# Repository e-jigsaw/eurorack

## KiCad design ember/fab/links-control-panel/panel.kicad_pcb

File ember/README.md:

# ember

Mutable Instruments モジュール群を tscircuit (TypeScript / React ベースの回路 + PCB 設計) に順次再構築するアセット集。

## 方針

- 単発移植ではなく、Eurorack 共通プリミティブと回路ブロックをアセットとして積み上げる
- EAGLE 資産を高忠実度で持ち上げる方向は採らない (PDF 再構築や Eagle 変換ツールは `../archive/` 配下)
- 「KiCad で書いたほうが速い」と感じても、アセット化を優先

## 試作台

Mutable Instruments **Links** v4.0 (4 HP、3 ブロック + 電源) を最初の実装ターゲットとする。

## 構成

- `primitives/` — 再利用コンポーネント (ジャック、電源ヘッダ、パネル等)
  - `jacks/pj301m-12.tsx` — Thonkiconn 3.5mm vertical mono jack ([詳細](primitives/jacks/pj301m-12.md))
- `links-control.circuit.tsx` — 制御面ボード。ジャック / LED / オス側インターコネクトヘッダのみ (100% THT、裸基板発注)
- `links-main.circuit.tsx` — メインボード。回路 / 電源 / メス側インターコネクトソケット (SMD、実装済み基板発注)

2 枚は `primitives/headers/interconnect-header.tsx` のヘッダ列で嵌合する (メインボードを裏返して制御面ボードに重ねる想定)。整合性は `bun run check:interconnect` で検証する (要ビルド後の `circuit.json`)。

## Links 単板試作

`links-single.circuit.tsx` は 19 × 108.4 mm・2層の単板版。ジャックと LED が表、回路と電源コネクタが裏。既存2枚基板の entry は残してある。

原典 EAGLE **回路図**から54部品・34ネットを抽出し、新しい配置を tscircuit で配線する。2026-09-10の修正でIC3/IC5の各電源に100nF（C11〜C14）を追加し、単板は58部品になった。原典 PCB の配線は取り込まない。入力ジャックの normal→GND、LED を含む帰還回路、電源の逆接保護を原典に合わせた。LM321 のピン番号と TSSOP の4.4 mm本体幅は単板版で明示している。

```bash
python3 scripts/extract-links-reference.py --check  # 原典と抽出データを照合
bun run typecheck
bun run build:single                              # 単板ビルド + 導通/DRC/DFM
bun run preview:single                            # 上記 + PCB/回路図 PNG
```

出力先は `dist/links-single/`。`check:single` は部品数・抵抗/容量値・原典とのネット一致に加え、実配線の導通と DRC を検証する。CLI がエラーを含んだまま終了コード0を返しても検証側で落とす。空の配線を DFM 合格として扱わない。

これは回路・配線の試作。両面GND面と10本の近接GNDビア接続を追加済み。各IC電源→100nFの実配線は1.725〜3.294 mm・ビア0、GNDパッド→近接ビアは0.9〜1.6 mm・幅0.3 mm。ビアから電源ヘッダまではtop GND面内に0.5 mm以上の幅の経路があることを幾何検査する。

配線長警告10件は残るが、GND面と近接ビアを含まない既存GND枝の長さであり、局所戻りの検査は別のゲートで行う。コネクタ向き警告5件は垂直挿入ジャックに対する既知の警告。製造承認や実機の発振・ノイズ検証を意味しない。

`modules/links/single-board/fixed-routes.json` はローカルルータ出力のビア間隔を個別修正し、GND接続を追加した経路入力。`fixed-router.ts` から通常のtscircuitインポート・銅箔生成・DRCに渡す。配線入力のbounds/障害物/ネットが変わるとSHA-256ガードで停止するため、部品配置・接続を変更した場合は経路を再生成・レビューして更新する。生成済みcircuit.jsonのエラーを書き換えて合格させる方式ではない。

GND面と局所経路の追加検査（Shapely 2.1.2、Python 3）:

```bash
python3 -m venv /tmp/links-geometry-venv
/tmp/links-geometry-venv/bin/pip install -r scripts/requirements-links-geometry.txt
/tmp/links-geometry-venv/bin/python scripts/check-links-decoupling.py dist/links-single/circuit.json
bunx tsci check shorts dist/links-single/circuit.json --mode gerber --pixels-per-mm 40
```

C1/C2 は原典と同じ公称4.7 µFを0805セラミックとして配置しており、実部品のDCバイアス特性と調達品番は未確定。ジャック寸法・パネル適合・部品の高さ・実機動作は現物検証が必要。旧2枚基板には旧LM321ピン定義と廃止された `sequential_trace` 設定が残っているため、旧版の過去のDRC合格を電気的正しさの証明として扱わない。

## 開発

```bash
bunx tsci dev      # http://localhost:3020 でライブプレビュー
bunx tsci build    # ビルド検証
bunx tsci snapshot # PCB / schematic SVG を __snapshots__/ に出力
```

## Linear

[tscircuit Eurorack](https://linear.app/cmsn/project/tscircuit-eurorack-cd01aea01d05) (Nok Audio initiative)

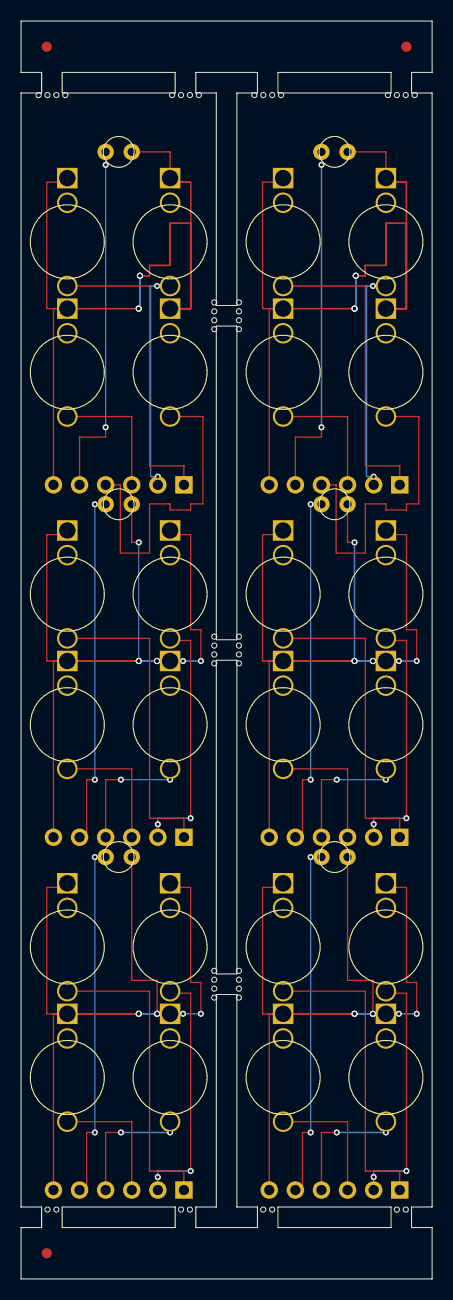
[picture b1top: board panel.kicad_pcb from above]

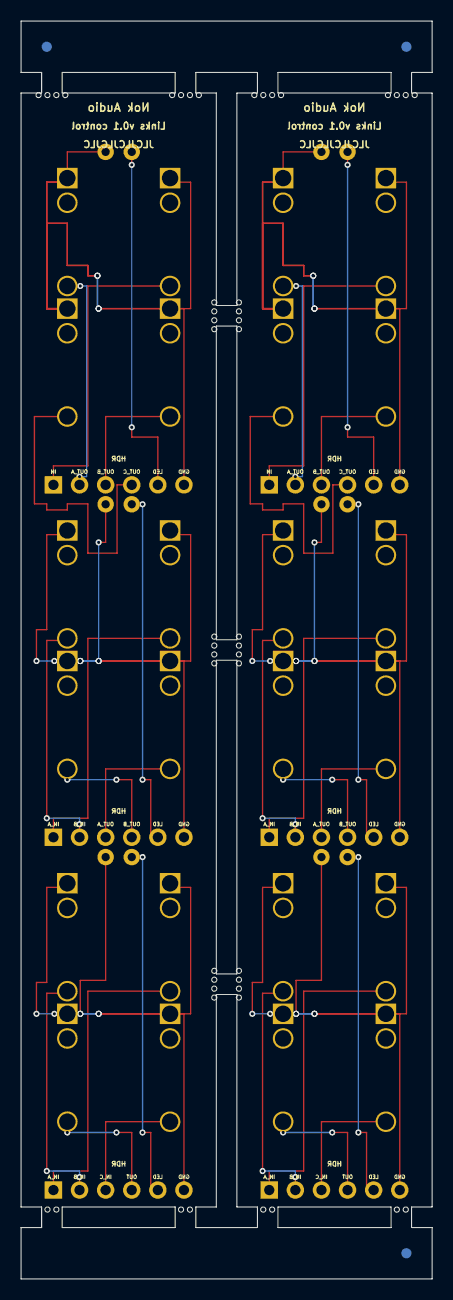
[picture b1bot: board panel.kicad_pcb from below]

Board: 2 copper layers, 40.0 x 122.4 mm, 90 parts (3 on the bottom side), 32 nets.

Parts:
HDR: HDR; pin_header_pinrow6_p2.54mm_id1mm_od1.7mm_male
HDR#2, HDR#3, HDR#4, HDR#5, HDR#6: HDR; pin_header_pinrow6_p2.54mm_id1mm_od1.7mm_male
J1, J1#2, J2, J2#2, J3, J3#2, J4, J4#2, J5, J5#2, J6, J6#2, J7, J7#2, J8, J8#2, J9, J9#2, J10, J10#2, J11, J11#2, J12, J12#2: PJ301M-12
KiKit_FID_B_1, KiKit_FID_B_2, KiKit_FID_B_3: Fiducial
KiKit_FID_T_1, KiKit_FID_T_2, KiKit_FID_T_3: Fiducial
KiKit_MB_1_1, KiKit_MB_1_2, KiKit_MB_1_3, KiKit_MB_1_4, KiKit_MB_2_1, KiKit_MB_2_2, KiKit_MB_2_3, KiKit_MB_2_4, KiKit_MB_3_1, KiKit_MB_3_2, KiKit_MB_3_3, KiKit_MB_3_4, KiKit_MB_4_1, KiKit_MB_4_2, KiKit_MB_4_3, KiKit_MB_4_4, KiKit_MB_5_1, KiKit_MB_5_2, KiKit_MB_5_3, KiKit_MB_5_4, KiKit_MB_6_1, KiKit_MB_6_2, KiKit_MB_6_3, KiKit_MB_6_4, KiKit_MB_7_1, KiKit_MB_7_2, KiKit_MB_7_3, KiKit_MB_7_4, KiKit_MB_8_1, KiKit_MB_8_2, KiKit_MB_8_3, KiKit_MB_8_4, KiKit_MB_9_1, KiKit_MB_9_2, KiKit_MB_9_3, KiKit_MB_9_4, KiKit_MB_10_1, KiKit_MB_10_2, KiKit_MB_10_3, KiKit_MB_10_4, KiKit_MB_11_2, KiKit_MB_11_3, KiKit_MB_12_2, KiKit_MB_12_3, KiKit_MB_13_2, KiKit_MB_13_3, KiKit_MB_14_2, KiKit_MB_14_3: NPTH
LED1, LED1#2, LED2, LED2#2, LED3, LED3#2: LED; led

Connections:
Board_0-.HDR > .LED to .LED1 > .anode: HDR#3.5, LED1.1
Board_0-.HDR > .LED to .LED2 > .anode: HDR#6.5, LED2#2.1
Board_0-.HDR > .LED to .LED3 > .anode: HDR#5.5, LED3#2.1
Board_0-.HDR > .OUT to .J12 > .TIP: HDR#5.4, J12#2.1
Board_0-.HDR > .OUT_A to .J2 > .TIP: HDR#3.2, J2#2.1
Board_0-.HDR > .OUT_A to .J7 > .TIP: HDR#6.3, J7.1
Board_0-.HDR > .OUT_B to .J3 > .TIP: HDR#3.3, J3#2.1
Board_0-.HDR > .OUT_B to .J8 > .TIP: HDR#6.4, J8#2.1
Board_0-.HDR > .OUT_C to .J4 > .TIP: HDR#3.4, J4.1
Board_0-.J1 > .TIP to .HDR > .IN: HDR#3.1, J1.1
Board_0-.J5 > .TIP to .HDR > .IN_A: HDR#6.1, J5.1
Board_0-.J6 > .TIP to .HDR > .IN_B: HDR#6.2, J6#2.1
Board_0-.J9 > .TIP to .HDR > .IN_A: HDR#5.1, J9#2.1
Board_0-.J10 > .TIP to .HDR > .IN_B: HDR#5.2, J10.1
Board_0-.J11 > .TIP to .HDR > .IN_C: HDR#5.3, J11#2.1
Board_0-GND: HDR#3.6, HDR#5.6, HDR#6.6, J1.3, J2#2.3, J3#2.3, J4.3, J5.3, J6#2.3, J7.3, J8#2.3, J9#2.3, J10.3, J11#2.3, J12#2.3, LED1.2, LED2#2.2, LED3#2.2
Board_1-.HDR > .LED to .LED1 > .anode: HDR.5, LED1#2.1
Board_1-.HDR > .LED to .LED2 > .anode: HDR#4.5, LED2.1
Board_1-.HDR > .LED to .LED3 > .anode: HDR#2.5, LED3.1
Board_1-.HDR > .OUT to .J12 > .TIP: HDR#2.4, J12.1
Board_1-.HDR > .OUT_A to .J2 > .TIP: HDR.2, J2.1
Board_1-.HDR > .OUT_A to .J7 > .TIP: HDR#4.3, J7#2.1
Board_1-.HDR > .OUT_B to .J3 > .TIP: HDR.3, J3.1
Board_1-.HDR > .OUT_B to .J8 > .TIP: HDR#4.4, J8.1
Board_1-.HDR > .OUT_C to .J4 > .TIP: HDR.4, J4#2.1
Board_1-.J1 > .TIP to .HDR > .IN: HDR.1, J1#2.1
Board_1-.J5 > .TIP to .HDR > .IN_A: HDR#4.1, J5#2.1
Board_1-.J6 > .TIP to .HDR > .IN_B: HDR#4.2, J6.1
Board_1-.J9 > .TIP to .HDR > .IN_A: HDR#2.1, J9.1
Board_1-.J10 > .TIP to .HDR > .IN_B: HDR#2.2, J10#2.1
Board_1-.J11 > .TIP to .HDR > .IN_C: HDR#2.3, J11.1
Board_1-GND: HDR.6, HDR#2.6, HDR#4.6, J1#2.3, J2.3, J3.3, J4#2.3, J5#2.3, J6.3, J7#2.3, J8.3, J9.3, J10#2.3, J11.3, J12.3, LED1#2.2, LED2.2, LED3.2

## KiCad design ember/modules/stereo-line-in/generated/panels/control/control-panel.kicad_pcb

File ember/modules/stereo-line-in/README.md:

# Stereo Line In / PCB rev F

2ch・4HPの試作用PCB。パネル平行の操作基板18×77mm（2層）とメイン基板18×110mm（4層）。

- 回路・値・接続: `model.ts`。部品選定: `procurement/selected-parts.json`。
- tscircuit PCB: `pcb/index.tsx`、`footprints.tsx`、`layout.json`。
- 配線済みの入口: `control.circuit.tsx` / `main.circuit.tsx`。`bun run dev` で開く。
- 全体図・出力: `generated/pcb/review.html`。各基板のGerber ZIP、JLC BOM/CPL、全実装表、KiCad PCB、実装図、検証JSONを同じフォルダに収録。
- 設計仕様・計画はRillのemberプロジェクト: `docs/superpowers/specs/2026-09-12-stereo-line-in-design.md`、`docs/superpowers/specs/2026-09-13-stereo-line-in-jack-mounting-design.md`、`docs/superpowers/plans/2026-09-13-stereo-line-in-pcb.md`。初期実装はFyr #712、ソケット化はFyr #716、上下端配置はFyr #717、ポット下向きはFyr #719。Rillは今回の接合変更を未反映（ページCRUDツールが未公開）。

## 再生成

このディレクトリで実行する。BunとKiCad 9 CLIが必要。macOSの標準KiCad配置を既定にしている。

```sh
bun install --frozen-lockfile
python3 -m venv .venv
.venv/bin/pip install -r requirements-pcb.txt
.venv/bin/python pcb/rebuild.py
```

`pcb/rebuild.py` は部品値とカタログ属性、全パッド座標、実際の銅箔接続/短絡/隙間、tscircuitの表示と製造用銅箔の一致、KiCad DRCを確認してから出力する。Gerber、ドリル、CPLは基板左下原点（X右、Y上）。CPLの部品ゼロ角度は独自フットプリント基準なので、JLCの実装プレビューで品番ごとの向きを確認する。

配線はローカルFreerouting 2.4.1 / Java 25で生成したDSN/SESを固定。`pcb/cached-router.ts` がその検証済み銅箔をtscircuitへ戻す。部品配置・ランド・接続の変更を検出したら古い配線の再利用を拒否する。新たに配線するときは `pcb/dsn.py` でDSNを作り、Freeroutingへ渡す。既存の固定経路 `route-fixes.json` と局所修正 `route-adjustments.json` は変更後の形状へ再確認が必要。検査を通した新しい配線についてのみ `frozen-routes.json` と `routing-cache.json` を更新する。

## 検証範囲

全105部品、323パッド、基板別83ネットの接続を確認。2枚とも短絡・未配線・クリアランス違反0、KiCad DRC 0。71個の抵抗・コンデンサは公称値と保存済みJLC属性が一致。LED電源のR_LED_SUPPLYは47Ω / C23182へ修正済み。JLC対象は30型番87部品、LED8個を含む18部品は別途手実装（ヘッダ2個・ソケット2個を含む）。在庫の根拠は2026-09-13の保存データで、予約ではない。

これは試作用の製造データで、JLCへのアップロード・実装向き/DFM確認、現物のジャックとポットの座面、ソケットの保持力・嵌合公差/はんだ高さ、実機の音声性能は未確認。機能SPICEの7ケースは `generated/verification.json` に記録済みで、メーカー実部品モデルによる検証ではない。3Dタブには `pcb/cad-models.ts` の公称外形・高さによる簡略モデルを表示する。ジャック・ポットは外形ブロック、端子は模式形状で、メーカーSTEP、軸・口金・実際のLED取付高さを再現した完成品CADではない。

## 基板間の接合（rev F）

control裏面にTSW-104-07-L-Dを2個、main表面にSSW-104-01-F-Dを2個実装。パネル基準の中心は上側(10,12)mm、下側(10,81)mm。両側とも長軸が横。16本の手配線と中央スペーサを廃止した。両方のポットはパネル正面から見て3本の信号端子が下を向く0度配置。controlの外形は元の18×77mmを維持した。パネル上端からの中心位置は3.5mmジャック22mm、LED32/37/42/47mm、gain L 56mm、gain R 69.5mm。1/4インチ入力は93/111mmを維持。

基板間隔12.4mmはパネルに固定するジャック/ポットの座面で決まる。ヘッダ樹脂2.54mm＋露出ピン5.84mm＋ソケット8.51mmなので挿入量は4.49mm（指定3.68〜6.35mm内）。樹脂同士は1.35mm離れる。樹脂が当たるまで押し込まない。パネル部品を仮組みして間隔を確認してからコネクタを手はんだする。コネクタ保持力・実寸公差の積み上げは現物未検証。

`pcb/check-assembly.py` は上下16ピンの座標・ネット、両基板の部品外形、基板裏に出る足とはんだを含めた突出1.5mmの領域を検査する。フィルムコンデンサとcontrol裏面の公称隙間は2.4mm、突出1.5mmを差し引いた残りは0.9mm。これは公称値の検査で、製造公差を含む保証ではない。検査結果は `generated/pcb/assembly-validation.json`。

コネクタの部品番号・公称寸法・2026-09-14の公式出荷可能数表示は `procurement/interconnect-selection.json`。JLCの実装対象には含めず手実装とする。在庫予約はしていない。

## 面付けデータ

`generated/panels/control/` と `generated/panels/main/` に、それぞれ4枚を同方向に並べたパネルを生成する。controlは92×91mm・2層、mainは92×124mm・4層、厚さは両方1.6mm。四周5mmの捨て板、2mmのルーター間隔、マウスバイト、2mm工具穴、両面fiducialを含む。個片の検証済みパッド・配線・部品面・回転は変更せず複製する。

生成は `pcb/rebuild.py` の後に、同じShapely環境のPythonで `pcb/panelize.py` を実行する。面付けは単板を更新しただけでは再生成されない。`validation.json` の `source_sha256` で入力版を追跡できる。

各 `*-panel-order-files.zip` にGerber ZIP、4枚分のBOM/CPL、両面実装図、検証結果、発注条件をまとめた。JLCへは内包するGerber ZIPをアップロードし、BOM/CPLを別途指定する。外側の一式ZIPをGerberとしてアップロードしない。BOM/CPLのP1_〜P4_は既に4枚分なので、追加の繰り返し指定は不要。発注はPanel by Customer、controlはBottom実装、mainはBoth sides/Standardを想定。数量はパネル単位で、1パネルから各基板4枚を取り出す。

JLC側のルーター加工・タブDFM、部品対応と角度プレビュー、在庫は未確認。分割後はバリを除去して公称18mm幅に仕上げる。保持力と実装済みパネルの分割応力は実物で未検証。Fyr #720、Rill `docs/superpowers/plans/2026-09-14-stereo-line-in-panelization.md` に記録。

### Silkscreen and references

`pcb/reference-aliases.json` maps internal descriptive references to compact printed references (R1, C1, etc.). `generated/schematic.svg` uses the same short references; source JSON and JLC BOM/CPL keep internal names. See `generated/reference-guide.html` for all 105 board placements, including the two connectors on each board that are outside the logical audio schematic. Some labels sit under components and are for assembly identification.

`pcb/add-silkscreen.py` generates `pcb/silkscreen.json` and reserves an exposed 5×5 mm solid bottom silkscreen square on each unit. Select 5×5 mm 2D barcode and Specify Position at JLCPCB; this is not a copper square. Main bottom carries Nok Audio and Xof v0.1. The Japanese product name is 左右波形増幅器. Full rebuild regenerates silkscreen; rerun `pcb/panelize.py` afterward.

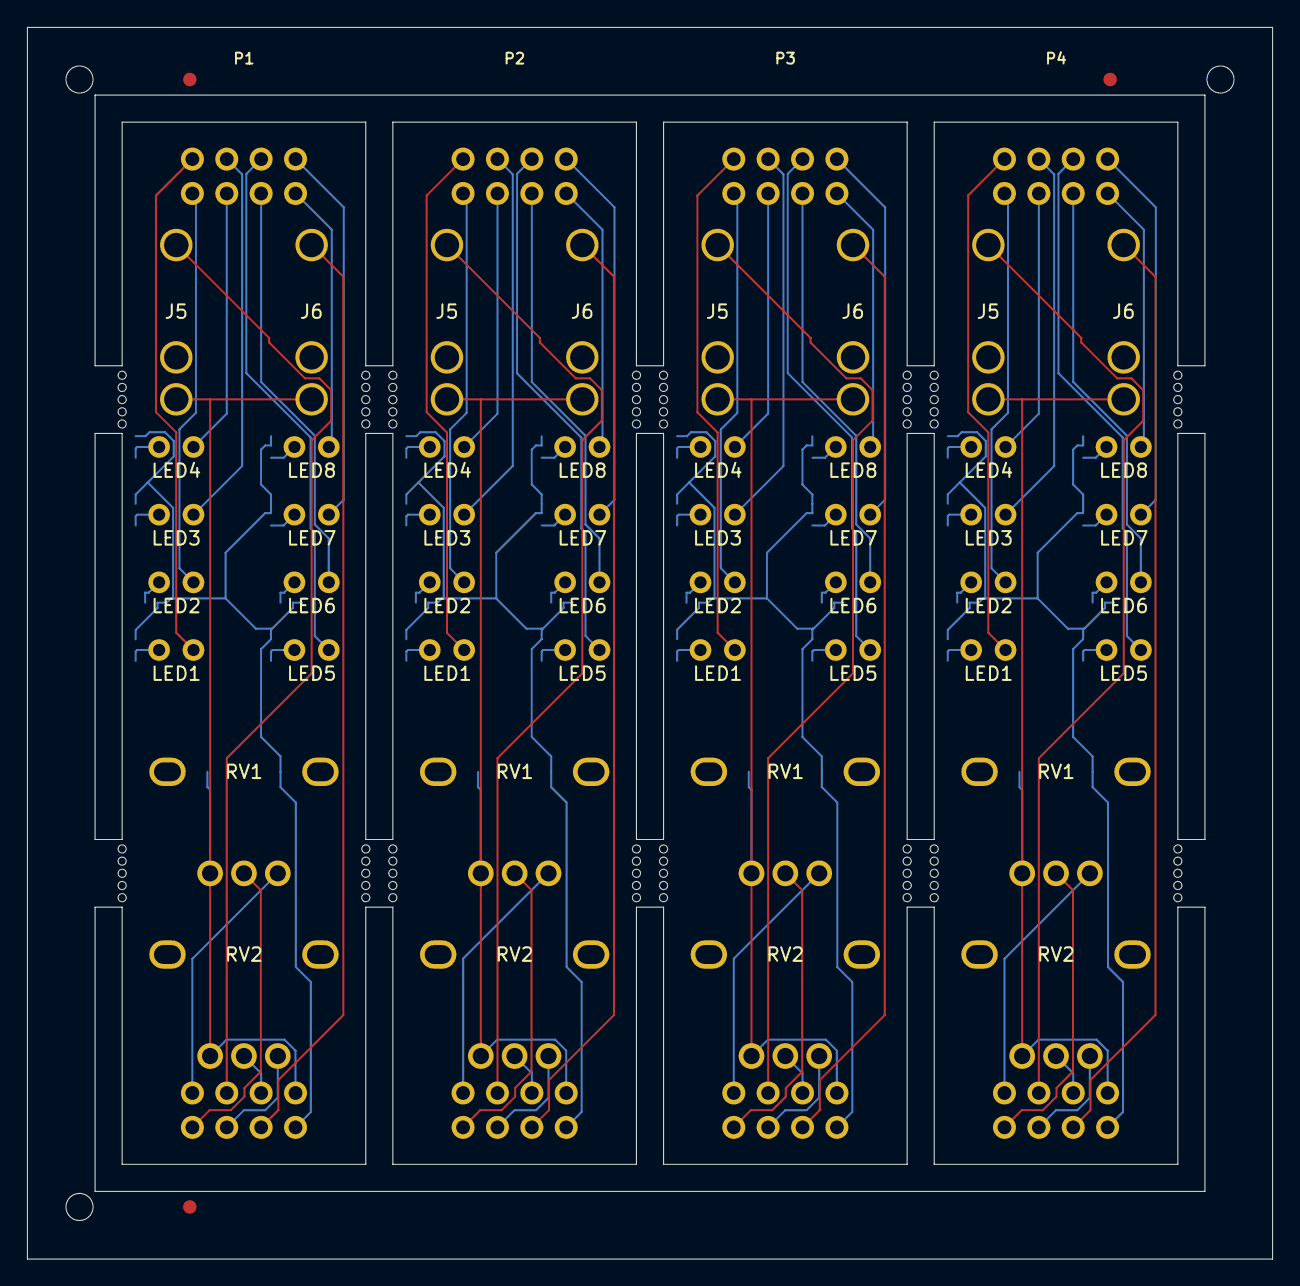
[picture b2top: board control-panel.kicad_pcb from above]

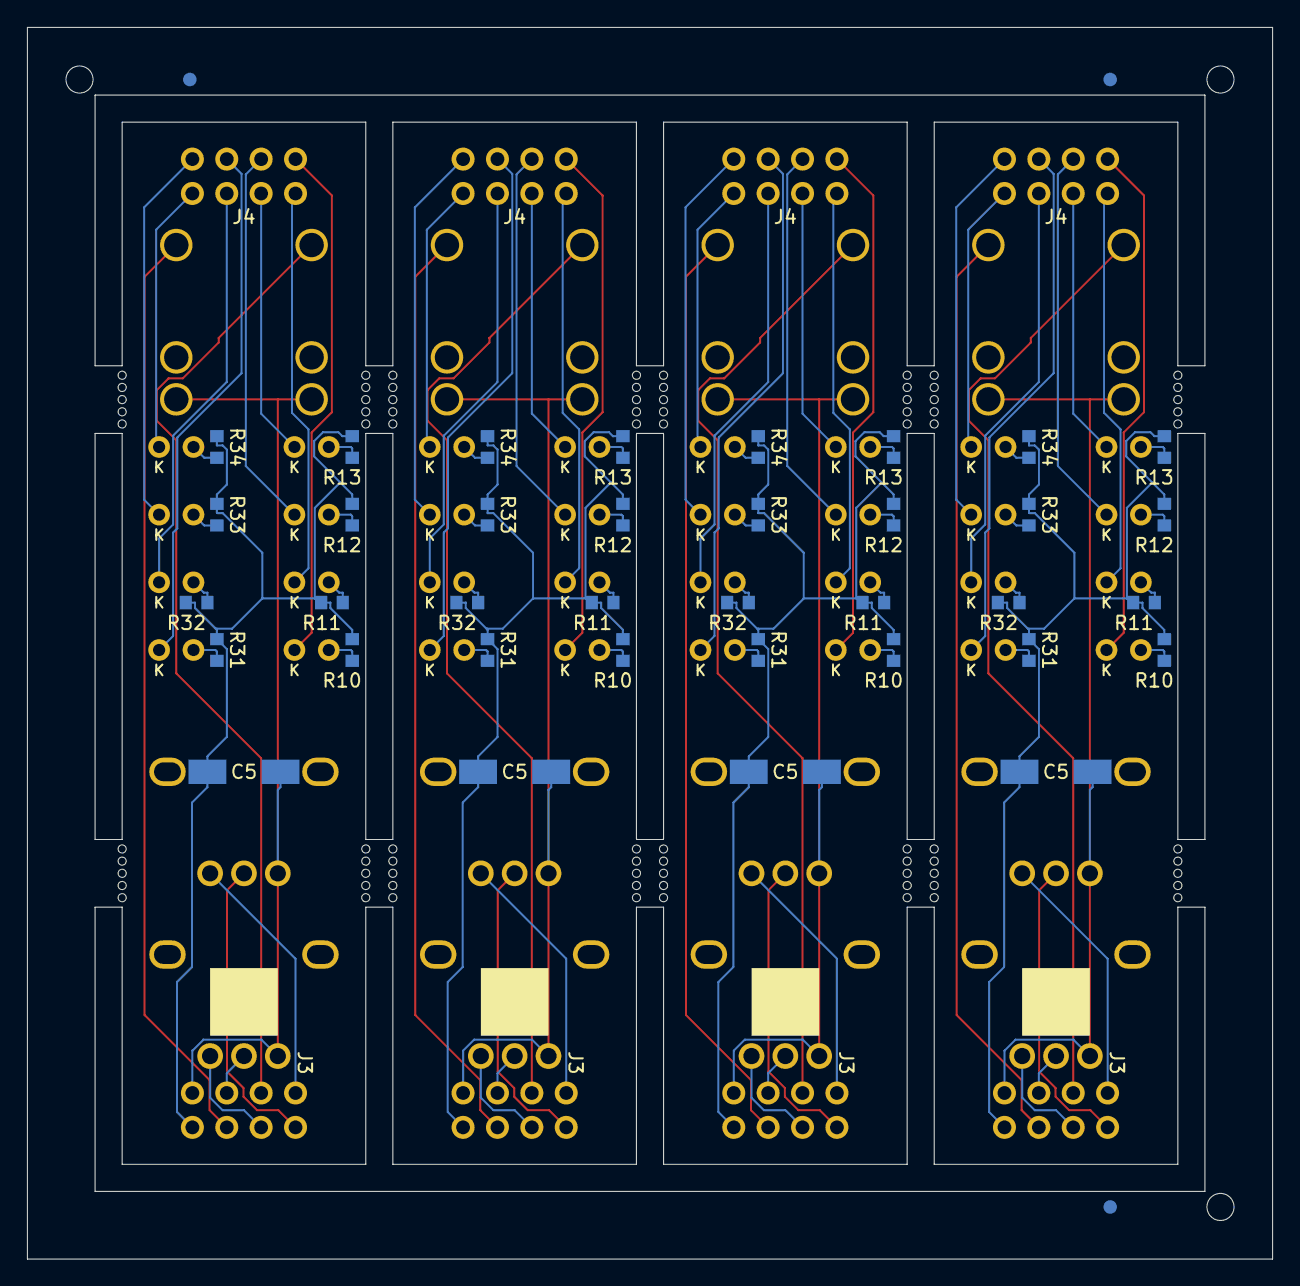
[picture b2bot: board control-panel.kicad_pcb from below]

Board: 2 copper layers, 92.0 x 91.0 mm, 181 parts (47 on the bottom side), 96 nets.

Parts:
FIDB1, FIDB2, FIDB3: Panel_Fiducial
FIDF1, FIDF2, FIDF3: Panel_Fiducial
MB1, MB2, MB3, MB4, MB5, MB6, MB7, MB8, MB9, MB10, MB11, MB12, MB13, MB14, MB15, MB16, MB17, MB18, MB19, MB20, MB21, MB22, MB23, MB24, MB25, MB26, MB27, MB28, MB29, MB30, MB31, MB32, MB33, MB34, MB35, MB36, MB37, MB38, MB39, MB40, MB41, MB42, MB43, MB44, MB45, MB46, MB47, MB48, MB49, MB50, MB51, MB52, MB53, MB54, MB55, MB56, MB57, MB58, MB59, MB60, MB61, MB62, MB63, MB64, MB65, MB66, MB67, MB68, MB69, MB70, MB71, MB72, MB73, MB74, MB75, MB76, MB77, MB78, MB79, MB80: Panel_NPTH
P1_C_LED_BULK, P2_C_LED_BULK, P3_C_LED_BULK, P4_C_LED_BULK: RVT1E470M0605; SMD,D6.3xL5.4mm
P1_J_LINK_BOTTOM, P1_J_LINK_TOP, P2_J_LINK_BOTTOM, P2_J_LINK_TOP, P3_J_LINK_BOTTOM, P3_J_LINK_TOP, P4_J_LINK_BOTTOM, P4_J_LINK_TOP: TSW-104-07-L-D; TSW-2x4
P1_J_OUT_L, P1_J_OUT_R, P2_J_OUT_L, P2_J_OUT_R, P3_J_OUT_L, P3_J_OUT_R, P4_J_OUT_L, P4_J_OUT_R: WQP-WQP518MA; WQP
P1_LED_L_1, P1_LED_L_2, P1_LED_R_1, P1_LED_R_2, P2_LED_L_1, P2_LED_L_2, P2_LED_R_1, P2_LED_R_2, P3_LED_L_1, P3_LED_L_2, P3_LED_R_1, P3_LED_R_2, P4_LED_L_1, P4_LED_L_2, P4_LED_R_1, P4_LED_R_2: XL-302UGD; LED3
P1_LED_L_3, P1_LED_R_3, P2_LED_L_3, P2_LED_R_3, P3_LED_L_3, P3_LED_R_3, P4_LED_L_3, P4_LED_R_3: TZ-L2-03YYBY2YDJ30-001; LED3
P1_LED_L_4, P1_LED_R_4, P2_LED_L_4, P2_LED_R_4, P3_LED_L_4, P3_LED_R_4, P4_LED_L_4, P4_LED_R_4: XL-302SURD; LED3
P1_RV_L, P1_RV_R, P2_RV_L, P2_RV_R, P3_RV_L, P3_RV_R, P4_RV_L, P4_RV_R: RV9312NO-KQ15A6.0-B10K-060; Tayda
P1_R_L_LED_1, P1_R_L_LED_2, P1_R_L_LED_3, P1_R_L_LED_4, P1_R_R_LED_1, P1_R_R_LED_2, P1_R_R_LED_3, P1_R_R_LED_4, P2_R_L_LED_1, P2_R_L_LED_2, P2_R_L_LED_3, P2_R_L_LED_4, P2_R_R_LED_1, P2_R_R_LED_2, P2_R_R_LED_3, P2_R_R_LED_4, P3_R_L_LED_1, P3_R_L_LED_2, P3_R_L_LED_3, P3_R_L_LED_4, P3_R_R_LED_1, P3_R_R_LED_2, P3_R_R_LED_3, P3_R_R_LED_4, P4_R_L_LED_1, P4_R_L_LED_2, P4_R_L_LED_3, P4_R_L_LED_4, P4_R_R_LED_1, P4_R_R_LED_2, P4_R_R_LED_3, P4_R_R_LED_4: 0603WAF1002T5E; 0603
TOOL1, TOOL2, TOOL3: Panel_NPTH

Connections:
P1_GND: P1_C_LED_BULK.2, P1_J_LINK_BOTTOM.7, P1_J_OUT_L.2, P1_J_OUT_R.2, P1_RV_L.1, P1_RV_R.1
P1_L_LED_1_A: P1_LED_L_1.2, P1_R_L_LED_1.2
P1_L_LED_1_K: P1_J_LINK_TOP.1, P1_LED_L_1.1
P1_L_LED_2_A: P1_LED_L_2.2, P1_R_L_LED_2.2
P1_L_LED_2_K: P1_J_LINK_TOP.2, P1_LED_L_2.1
P1_L_LED_3_A: P1_LED_L_3.2, P1_R_L_LED_3.2
P1_L_LED_3_K: P1_J_LINK_TOP.3, P1_LED_L_3.1
P1_L_LED_4_A: P1_LED_L_4.2, P1_R_L_LED_4.2
P1_L_LED_4_K: P1_J_LINK_TOP.4, P1_LED_L_4.1
P1_L_OUT: P1_J_LINK_BOTTOM.3, P1_J_OUT_L.1
P1_L_RX_OUT: P1_J_LINK_BOTTOM.1, P1_RV_L.3
P1_L_WIPER: P1_J_LINK_BOTTOM.2, P1_RV_L.2
P1_R_LED_1_A: P1_LED_R_1.2, P1_R_R_LED_1.2
P1_R_LED_1_K: P1_J_LINK_TOP.5, P1_LED_R_1.1
P1_R_LED_2_A: P1_LED_R_2.2, P1_R_R_LED_2.2
P1_R_LED_2_K: P1_J_LINK_TOP.6, P1_LED_R_2.1
P1_R_LED_3_A: P1_LED_R_3.2, P1_R_R_LED_3.2
P1_R_LED_3_K: P1_J_LINK_TOP.7, P1_LED_R_3.1
P1_R_LED_4_A: P1_LED_R_4.2, P1_R_R_LED_4.2
P1_R_LED_4_K: P1_J_LINK_TOP.8, P1_LED_R_4.1
P1_R_OUT: P1_J_LINK_BOTTOM.6, P1_J_OUT_R.1
P1_R_RX_OUT: P1_J_LINK_BOTTOM.4, P1_RV_R.3
P1_R_WIPER: P1_J_LINK_BOTTOM.5, P1_RV_R.2
P1_VLED: P1_C_LED_BULK.1, P1_J_LINK_BOTTOM.8, P1_R_L_LED_1.1, P1_R_L_LED_2.1, P1_R_L_LED_3.1, P1_R_L_LED_4.1, P1_R_R_LED_1.1, P1_R_R_LED_2.1, P1_R_R_LED_3.1, P1_R_R_LED_4.1
P2_GND: P2_C_LED_BULK.2, P2_J_LINK_BOTTOM.7, P2_J_OUT_L.2, P2_J_OUT_R.2, P2_RV_L.1, P2_RV_R.1
P2_L_LED_1_A: P2_LED_L_1.2, P2_R_L_LED_1.2
P2_L_LED_1_K: P2_J_LINK_TOP.1, P2_LED_L_1.1
P2_L_LED_2_A: P2_LED_L_2.2, P2_R_L_LED_2.2
P2_L_LED_2_K: P2_J_LINK_TOP.2, P2_LED_L_2.1
P2_L_LED_3_A: P2_LED_L_3.2, P2_R_L_LED_3.2
P2_L_LED_3_K: P2_J_LINK_TOP.3, P2_LED_L_3.1
P2_L_LED_4_A: P2_LED_L_4.2, P2_R_L_LED_4.2
P2_L_LED_4_K: P2_J_LINK_TOP.4, P2_LED_L_4.1
P2_L_OUT: P2_J_LINK_BOTTOM.3, P2_J_OUT_L.1
P2_L_RX_OUT: P2_J_LINK_BOTTOM.1, P2_RV_L.3
P2_L_WIPER: P2_J_LINK_BOTTOM.2, P2_RV_L.2
P2_R_LED_1_A: P2_LED_R_1.2, P2_R_R_LED_1.2
P2_R_LED_1_K: P2_J_LINK_TOP.5, P2_LED_R_1.1
P2_R_LED_2_A: P2_LED_R_2.2, P2_R_R_LED_2.2
P2_R_LED_2_K: P2_J_LINK_TOP.6, P2_LED_R_2.1
P2_R_LED_3_A: P2_LED_R_3.2, P2_R_R_LED_3.2
P2_R_LED_3_K: P2_J_LINK_TOP.7, P2_LED_R_3.1
P2_R_LED_4_A: P2_LED_R_4.2, P2_R_R_LED_4.2
P2_R_LED_4_K: P2_J_LINK_TOP.8, P2_LED_R_4.1
P2_R_OUT: P2_J_LINK_BOTTOM.6, P2_J_OUT_R.1
P2_R_RX_OUT: P2_J_LINK_BOTTOM.4, P2_RV_R.3
P2_R_WIPER: P2_J_LINK_BOTTOM.5, P2_RV_R.2
P2_VLED: P2_C_LED_BULK.1, P2_J_LINK_BOTTOM.8, P2_R_L_LED_1.1, P2_R_L_LED_2.1, P2_R_L_LED_3.1, P2_R_L_LED_4.1, P2_R_R_LED_1.1, P2_R_R_LED_2.1, P2_R_R_LED_3.1, P2_R_R_LED_4.1
P3_GND: P3_C_LED_BULK.2, P3_J_LINK_BOTTOM.7, P3_J_OUT_L.2, P3_J_OUT_R.2, P3_RV_L.1, P3_RV_R.1
P3_L_LED_1_A: P3_LED_L_1.2, P3_R_L_LED_1.2
P3_L_LED_1_K: P3_J_LINK_TOP.1, P3_LED_L_1.1
P3_L_LED_2_A: P3_LED_L_2.2, P3_R_L_LED_2.2
P3_L_LED_2_K: P3_J_LINK_TOP.2, P3_LED_L_2.1
P3_L_LED_3_A: P3_LED_L_3.2, P3_R_L_LED_3.2
P3_L_LED_3_K: P3_J_LINK_TOP.3, P3_LED_L_3.1
P3_L_LED_4_A: P3_LED_L_4.2, P3_R_L_LED_4.2
P3_L_LED_4_K: P3_J_LINK_TOP.4, P3_LED_L_4.1
P3_L_OUT: P3_J_LINK_BOTTOM.3, P3_J_OUT_L.1
P3_L_RX_OUT: P3_J_LINK_BOTTOM.1, P3_RV_L.3
P3_L_WIPER: P3_J_LINK_BOTTOM.2, P3_RV_L.2
P3_R_LED_1_A: P3_LED_R_1.2, P3_R_R_LED_1.2
P3_R_LED_1_K: P3_J_LINK_TOP.5, P3_LED_R_1.1
P3_R_LED_2_A: P3_LED_R_2.2, P3_R_R_LED_2.2
P3_R_LED_2_K: P3_J_LINK_TOP.6, P3_LED_R_2.1
P3_R_LED_3_A: P3_LED_R_3.2, P3_R_R_LED_3.2
P3_R_LED_3_K: P3_J_LINK_TOP.7, P3_LED_R_3.1
P3_R_LED_4_A: P3_LED_R_4.2, P3_R_R_LED_4.2
P3_R_LED_4_K: P3_J_LINK_TOP.8, P3_LED_R_4.1
P3_R_OUT: P3_J_LINK_BOTTOM.6, P3_J_OUT_R.1
P3_R_RX_OUT: P3_J_LINK_BOTTOM.4, P3_RV_R.3
P3_R_WIPER: P3_J_LINK_BOTTOM.5, P3_RV_R.2
P3_VLED: P3_C_LED_BULK.1, P3_J_LINK_BOTTOM.8, P3_R_L_LED_1.1, P3_R_L_LED_2.1, P3_R_L_LED_3.1, P3_R_L_LED_4.1, P3_R_R_LED_1.1, P3_R_R_LED_2.1, P3_R_R_LED_3.1, P3_R_R_LED_4.1
P4_GND: P4_C_LED_BULK.2, P4_J_LINK_BOTTOM.7, P4_J_OUT_L.2, P4_J_OUT_R.2, P4_RV_L.1, P4_RV_R.1
P4_L_LED_1_A: P4_LED_L_1.2, P4_R_L_LED_1.2
P4_L_LED_1_K: P4_J_LINK_TOP.1, P4_LED_L_1.1
P4_L_LED_2_A: P4_LED_L_2.2, P4_R_L_LED_2.2
P4_L_LED_2_K: P4_J_LINK_TOP.2, P4_LED_L_2.1
P4_L_LED_3_A: P4_LED_L_3.2, P4_R_L_LED_3.2
P4_L_LED_3_K: P4_J_LINK_TOP.3, P4_LED_L_3.1
P4_L_LED_4_A: P4_LED_L_4.2, P4_R_L_LED_4.2
P4_L_LED_4_K: P4_J_LINK_TOP.4, P4_LED_L_4.1
P4_L_OUT: P4_J_LINK_BOTTOM.3, P4_J_OUT_L.1
P4_L_RX_OUT: P4_J_LINK_BOTTOM.1, P4_RV_L.3
P4_L_WIPER: P4_J_LINK_BOTTOM.2, P4_RV_L.2
P4_R_LED_1_A: P4_LED_R_1.2, P4_R_R_LED_1.2
P4_R_LED_1_K: P4_J_LINK_TOP.5, P4_LED_R_1.1
P4_R_LED_2_A: P4_LED_R_2.2, P4_R_R_LED_2.2
P4_R_LED_2_K: P4_J_LINK_TOP.6, P4_LED_R_2.1
P4_R_LED_3_A: P4_LED_R_3.2, P4_R_R_LED_3.2
P4_R_LED_3_K: P4_J_LINK_TOP.7, P4_LED_R_3.1
P4_R_LED_4_A: P4_LED_R_4.2, P4_R_R_LED_4.2
P4_R_LED_4_K: P4_J_LINK_TOP.8, P4_LED_R_4.1
P4_R_OUT: P4_J_LINK_BOTTOM.6, P4_J_OUT_R.1
P4_R_RX_OUT: P4_J_LINK_BOTTOM.4, P4_RV_R.3
P4_R_WIPER: P4_J_LINK_BOTTOM.5, P4_RV_R.2
P4_VLED: P4_C_LED_BULK.1, P4_J_LINK_BOTTOM.8, P4_R_L_LED_1.1, P4_R_L_LED_2.1, P4_R_L_LED_3.1, P4_R_L_LED_4.1, P4_R_R_LED_1.1, P4_R_R_LED_2.1, P4_R_R_LED_3.1, P4_R_R_LED_4.1

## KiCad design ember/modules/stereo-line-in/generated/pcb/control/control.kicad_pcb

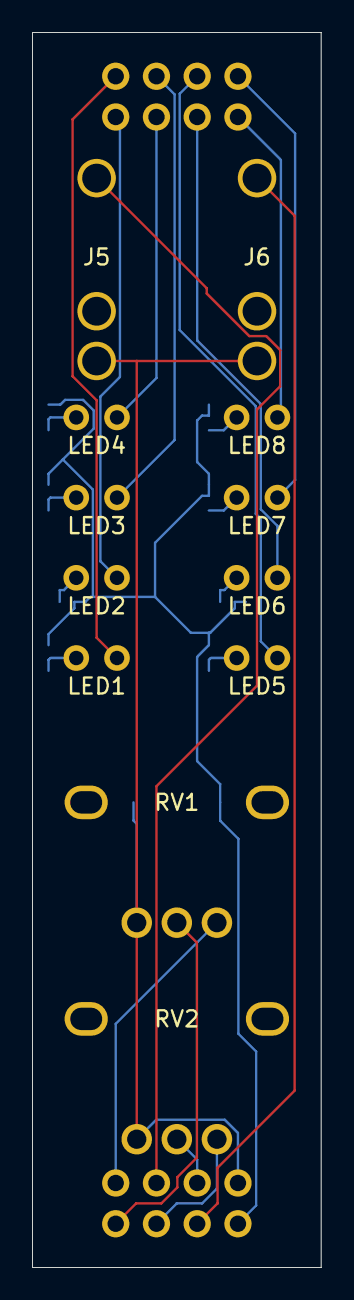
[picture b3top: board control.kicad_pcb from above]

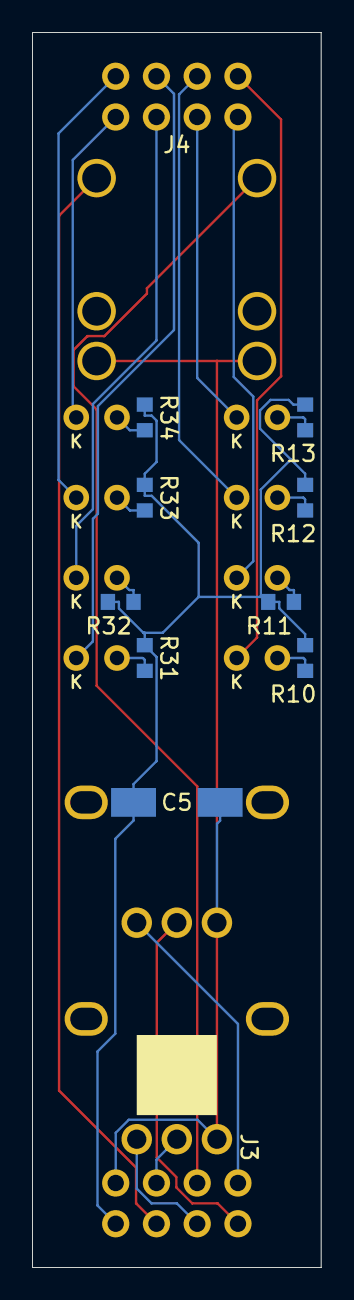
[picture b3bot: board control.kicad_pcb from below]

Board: 2 copper layers, 18.0 x 77.0 mm, 23 parts (11 on the bottom side), 24 nets.

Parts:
C_LED_BULK: RVT1E470M0605; SMD,D6.3xL5.4mm
J_LINK_BOTTOM: TSW-104-07-L-D; TSW-2x4
J_LINK_TOP: TSW-104-07-L-D; TSW-2x4
J_OUT_L: WQP-WQP518MA; WQP
J_OUT_R: WQP-WQP518MA; WQP
LED_L_1, LED_L_2: XL-302UGD; LED3
LED_L_3: TZ-L2-03YYBY2YDJ30-001; LED3
LED_L_4: XL-302SURD; LED3
LED_R_1, LED_R_2: XL-302UGD; LED3
LED_R_3: TZ-L2-03YYBY2YDJ30-001; LED3
LED_R_4: XL-302SURD; LED3
RV_L: RV9312NO-KQ15A6.0-B10K-060; Tayda
RV_R: RV9312NO-KQ15A6.0-B10K-060; Tayda
R_L_LED_1, R_L_LED_2, R_L_LED_3, R_L_LED_4: 0603WAF1002T5E; 0603
R_R_LED_1, R_R_LED_2, R_R_LED_3, R_R_LED_4: 0603WAF1002T5E; 0603

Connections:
GND: C_LED_BULK.2, J_LINK_BOTTOM.7, J_OUT_L.2, J_OUT_R.2, RV_L.1, RV_R.1
L_LED_1_A: LED_L_1.2, R_L_LED_1.2
L_LED_1_K: J_LINK_TOP.1, LED_L_1.1
L_LED_2_A: LED_L_2.2, R_L_LED_2.2
L_LED_2_K: J_LINK_TOP.2, LED_L_2.1
L_LED_3_A: LED_L_3.2, R_L_LED_3.2
L_LED_3_K: J_LINK_TOP.3, LED_L_3.1
L_LED_4_A: LED_L_4.2, R_L_LED_4.2
L_LED_4_K: J_LINK_TOP.4, LED_L_4.1
L_OUT: J_LINK_BOTTOM.3, J_OUT_L.1
L_RX_OUT: J_LINK_BOTTOM.1, RV_L.3
L_WIPER: J_LINK_BOTTOM.2, RV_L.2
R_LED_1_A: LED_R_1.2, R_R_LED_1.2
R_LED_1_K: J_LINK_TOP.5, LED_R_1.1
R_LED_2_A: LED_R_2.2, R_R_LED_2.2
R_LED_2_K: J_LINK_TOP.6, LED_R_2.1
R_LED_3_A: LED_R_3.2, R_R_LED_3.2
R_LED_3_K: J_LINK_TOP.7, LED_R_3.1
R_LED_4_A: LED_R_4.2, R_R_LED_4.2
R_LED_4_K: J_LINK_TOP.8, LED_R_4.1
R_OUT: J_LINK_BOTTOM.6, J_OUT_R.1
R_RX_OUT: J_LINK_BOTTOM.4, RV_R.3
R_WIPER: J_LINK_BOTTOM.5, RV_R.2
VLED: C_LED_BULK.1, J_LINK_BOTTOM.8, R_L_LED_1.1, R_L_LED_2.1, R_L_LED_3.1, R_L_LED_4.1, R_R_LED_1.1, R_R_LED_2.1, R_R_LED_3.1, R_R_LED_4.1
